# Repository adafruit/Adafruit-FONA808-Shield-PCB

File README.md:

## Adafruit FONA808 Shield PCB

<a href="http://www.adafruit.com/products/2636"><br/>
Click here to purchase one from the Adafruit shop</a>

PCB files for the Adafruit FONA808 Shield. Format is EagleCAD schematic and board layout
* https://www.adafruit.com/products/2636

### DESCRIPTION
Cellular + GPS tracking, all in one, for your Arduino? Oh yes! Introducing Adafruit FONA 808 GSM + GPS Shield, an all-in-one cellular phone module with that lets you add location-tracking, voice, text, SMS and data to your project, in Arduino shield format for easy use.

If you want a version without GPS, check out the FONA 800 Shield [here](https://www.adafruit.com/product/2468).

If you don't need the shield format, we also have this is a petite breakout [here](https://www.adafruit.com/product/2542).

If you just want a plain FONA, [click here](https://www.adafruit.com/product/1946).

This shield fits right over your Arduino or compatible. At the heart is a powerful GSM cellular module (we use the latest SIM808) with integrated GPS. This module can do just about everything

- Quad-band 850/900/1800/1900MHz - connect onto any global GSM network with any 2G SIM (in the USA, T-Mobile is suggested)
- Fully-integrated GPS (MT3337 chipset with -165 dBm tracking sensitivity) that can be controlled and query over the same serial port
- Make and receive voice calls using a headset or an external 32Ω speaker + electret microphone
- Send and receive SMS messages
- Send and receive GPRS data (TCP/IP, HTTP, etc.)
- PWM/Buzzer vibrational motor control
- AT command interface with "auto baud" detection

### License

Adafruit invests time and resources providing this open source design, please support Adafruit and open-source hardware by purchasing products from [Adafruit.com](https://www.adafruit.com)!

Designed by Adafruit Industries. 

Creative Commons Attribution, Share-Alike license, check license.txt for more information All text above must be included in any redistribution - see license.txt for more information.

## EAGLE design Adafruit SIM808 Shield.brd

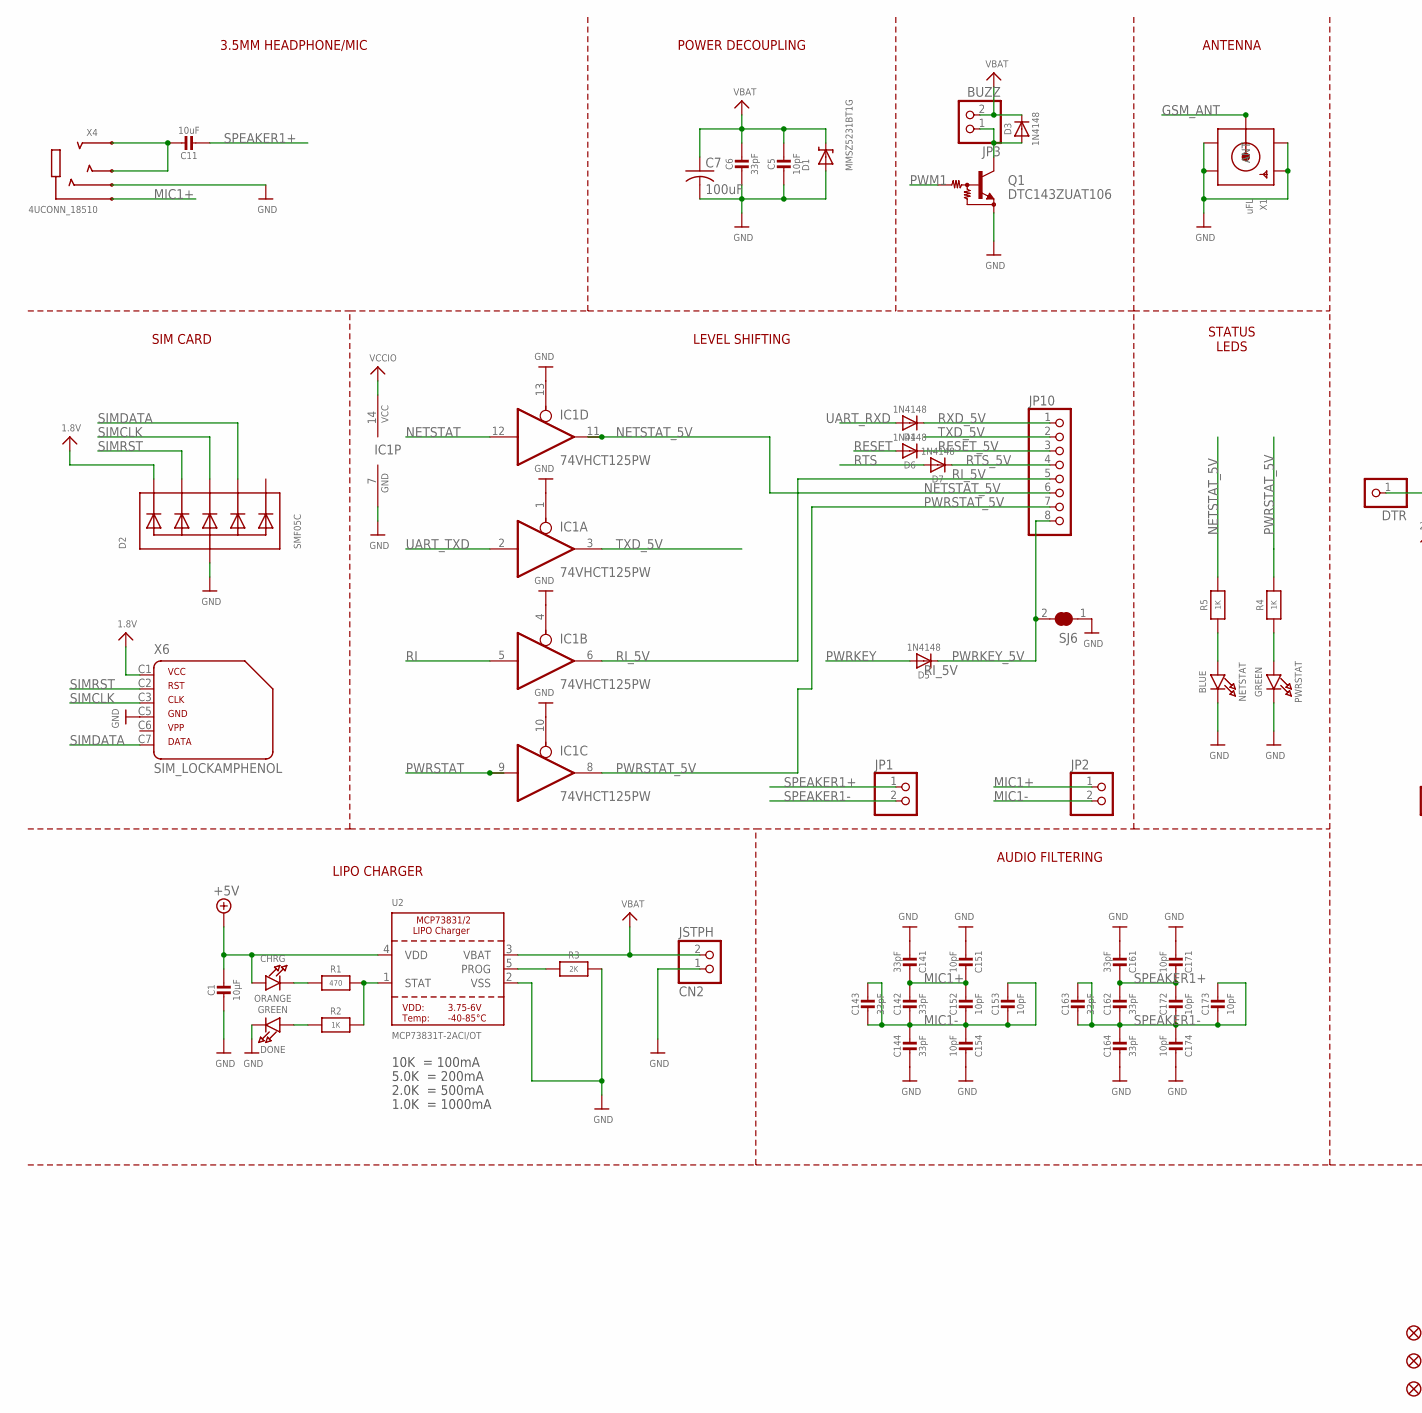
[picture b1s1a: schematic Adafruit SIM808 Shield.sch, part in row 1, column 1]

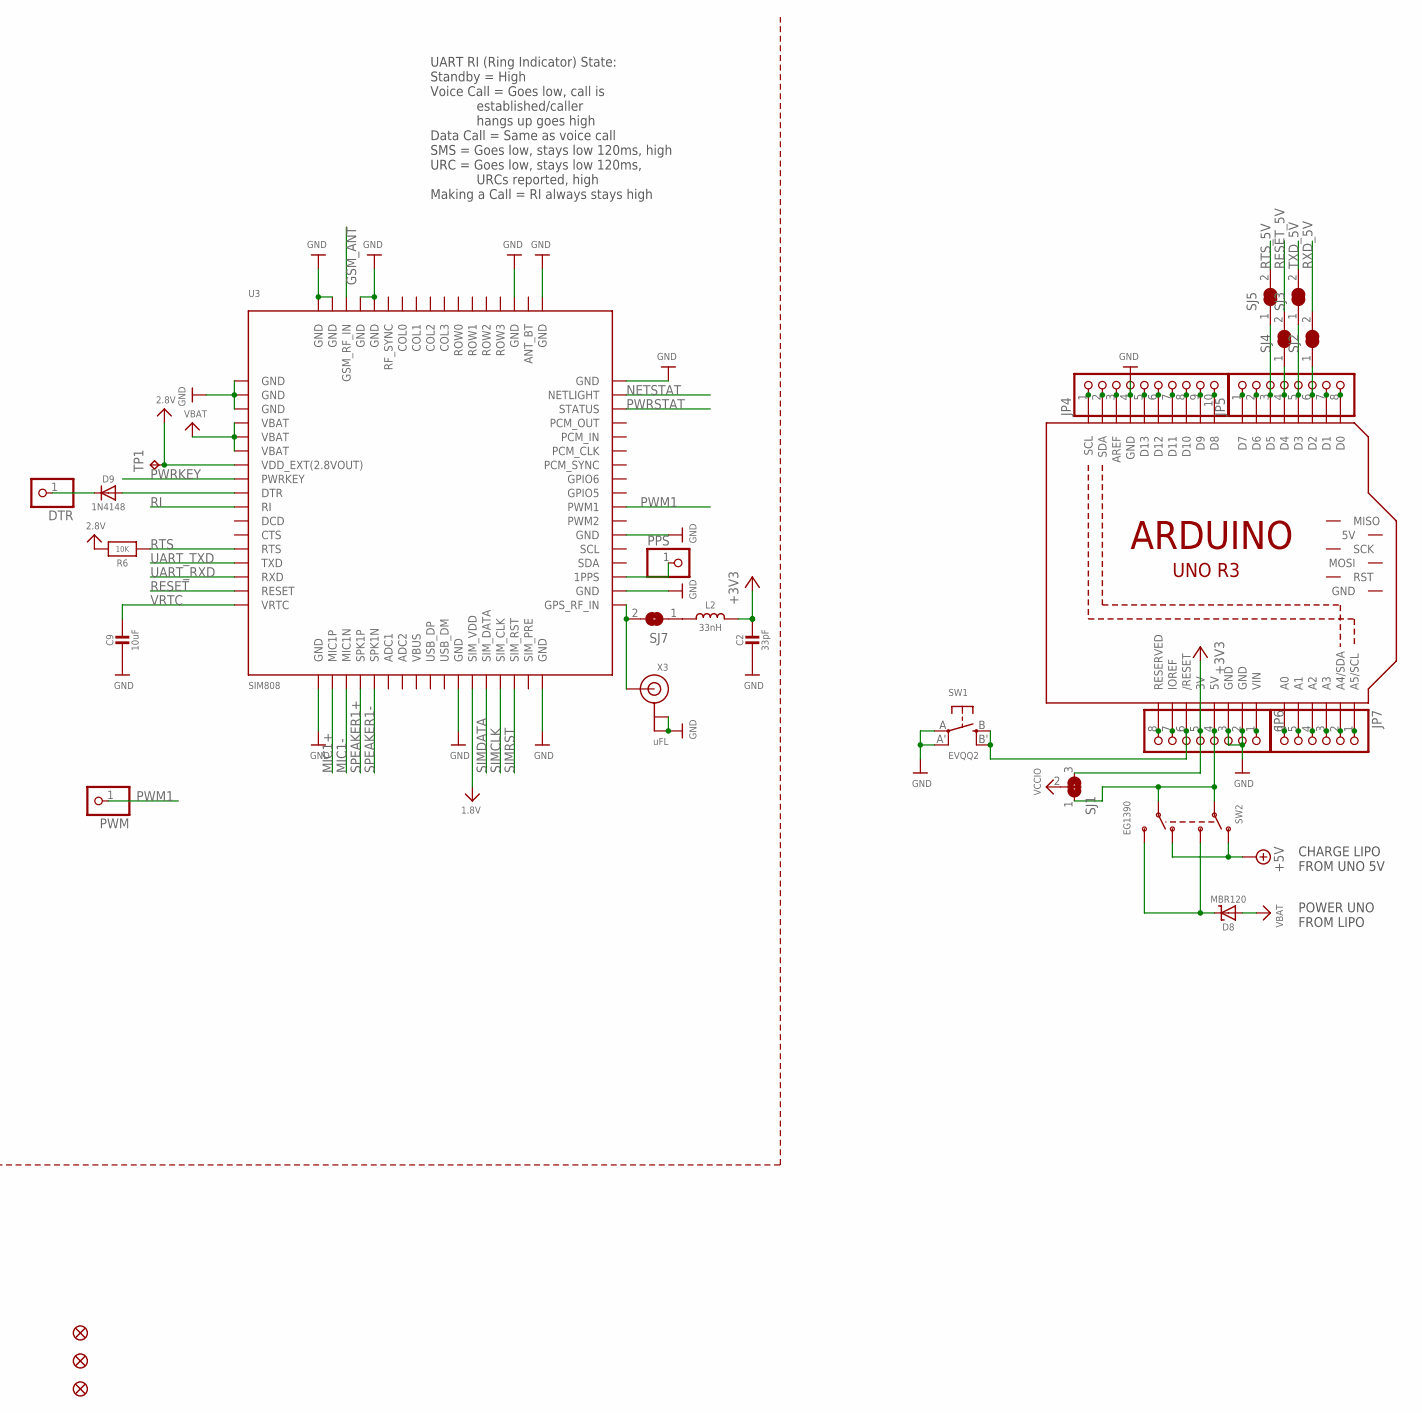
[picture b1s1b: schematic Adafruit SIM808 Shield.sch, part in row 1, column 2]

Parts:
C1: 10µF; 0805-NO
C2, C6: 33pF; 0805-NO
C5: 10pF; 0805-NO
C7: 100uF; C1210
C9, C11: 10uF; 0805-NO
C14, C16: 33pF; RESPACK_4X0603
C15, C17: 10pF; RESPACK_4X0603
CHRG: ORANGE; CHIPLED_0805_NOOUTLINE
CN2: JSTPH; JSTPH2
D1: MMSZ5231BT1G; SOD-123
D2: SMF05C; SOT363
D3, D4, D5, D6, D7, D9: 1N4148; SOD-323
D8: MBR120; SOD-123
DONE: GREEN; CHIPLED_0805_NOOUTLINE
DTR: PINHD-1X1CB; 1X01-CLEANBIG
FID1, FID2, FID3: FIDUCIAL""; FIDUCIAL_1MM
IC1: 74VHCT125PW; TSSOP14
JP1, JP2: HEADER-1X2ROUND; 1X02_ROUND
JP3: BUZZ; 1X02_ROUND
JP4: HEADER-1X1070MIL; 1X10_ROUND70
JP5, JP6: HEADER-1X876MIL; 1X08_ROUND_76
JP7: HEADER-1X676MIL; 1X06_ROUND_76
JP10: HEADER-1X870MIL; 1X08_ROUND_70
L2: 33nH; _0805MP
M1: ARDUINO_R3_ICSP_NODIM; ARDUINOR3_ICSP_NODIM
NETSTAT: BLUE; CHIPLED_0805_NOOUTLINE
PPS: PINHD-1X1CB; 1X01-CLEANBIG
PWM: PINHD-1X1CB; 1X01-CLEANBIG
PWRSTAT: GREEN; CHIPLED_0805_NOOUTLINE
Q1: DTC143ZUAT106; SC59-BEC
R1: 470; 0805-NO
R2, R4, R5: 1K; 0805-NO
R3: 2K; 0805-NO
R6: 10K; 0805-NO
SJ1: SOLDERJUMPER_2WAY; SOLDERJUMPER_2WAY_OPEN_NOPASTE
SJ2, SJ3, SJ4, SJ5, SJ6: SOLDERJUMPER_CLOSED; SOLDERJUMPER_CLOSEDWIRE
SJ7: SOLDERJUMPER; SOLDERJUMPER_ARROW_NOPASTE
SW1: EVQQ2; EVQ-Q2
SW2: EG1390
TP1: TPTP11R; TP11R
U2: MCP73831T-2ACI/OT; SOT23-5
U3: SIM808; SIM900_SMT
X1: uFL; SMA_EDGELAUNCH_UFL
X3: uFL; U.FL
X4: 4UCONN_18510
X6: SIM_LOCKAMPHENOL; C707_10M006_512_2

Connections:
1.8V: D2.1 (C1), U3.P$29 (SIM_VDD), X6.C1 (1)
2.8V: R6.2, TP1.TP, U3.P$7 (VDD_EXT(2.8VOUT))
5V: JP6.4, M1.5V, SJ1.1, SW2.P1, SW2.P2
+3V3: C2.1, JP6.5, L2.2, M1.3V, SJ1.3
+5V: C1.1, CHRG.A, SW2.O1, SW2.O2, U2.4 (VDD)
A0: JP7.6, M1.A0
A1: JP7.5, M1.A1
A2: JP7.4, M1.A2
A3: JP7.3, M1.A3
A4: JP7.2, M1.A4 (A4/SDA)
A5: JP7.1, M1.A5 (A5/SCL)
AREF: JP4.3, M1.AREF
BUZZ-: D3.A, JP3.1, Q1.C
D0: JP5.8, M1.D0
D1: JP5.7, M1.D1
D2: JP5.6, M1.D2, SJ2.1
D3: JP5.5, M1.D3, SJ3.1
D4: JP5.4, M1.D4, SJ4.1
D5: JP5.3, M1.D5, SJ5.1
D6: JP5.2, M1.D6
D7: JP5.1, M1.D7
D8: JP4.10, M1.D8
D9: JP4.9, M1.D9
D10: JP4.8, M1.D10
D11: JP4.7, M1.D11
D12: JP4.6, M1.D12
D13: JP4.5, M1.D13
DTR_5V: D9.C, DTR.1
GND: C1.2, C2.2, C5.2, C6.2, C7.2, C9.2, C14.5 (2), C14.8 (2), C15.4 (1), C15.8 (2), C16.5 (2), C16.8 (2), C17.4 (1), C17.8 (2), CN2.1, D1.A, D2.2 (A), DONE.C, IC1.1 (OE), IC1.4 (OE), IC1.7 (GND), IC1.10 (OE), IC1.13 (OE), JP4.4, JP6.2, JP6.3, M1.GND, M1.GND@1 (GND), M1.GND@3 (GND), NETSTAT.C, PWRSTAT.C, Q1.E, R3.2, SJ6.1, SW1.A, SW1.A' (P1), U2.2 (VSS), U3.P$1 (GND), U3.P$2 (GND), U3.P$3 (GND), U3.P$18 (GND), U3.P$28 (GND), U3.P$34 (GND), U3.P$36 (GND), U3.P$40 (GND), U3.P$51 (GND), U3.P$52 (GND), U3.P$54 (GND), U3.P$64 (GND), U3.P$65 (GND), U3.P$67 (GND), U3.P$68 (GND), X1.GND@1 (GND1), X1.GND@2 (GND2), X1.GND@3 (GND3), X1.GND@4 (GND4), X3.1 (GND), X3.2 (GND), X4.4-INNER_SLEEVE (RING1), X6.C5 (4)
GPS_PPS: PPS.1, U3.P$37 (1PPS)
GSM_ANT: U3.P$66 (GSM_RF_IN), X1.P (ANT)
HP+: C11.1, X4.2-TIP (RING3), X4.3-OUTER_SLEEVE (RING2)
IOREF: JP6.7, M1.IOREF
MIC1+: C14.1, C14.2 (1), C15.1, C15.2 (1), JP2.1, U3.P$19 (MIC1P), X4.1-GND (TIP)
MIC1-: C14.3 (1), C14.4 (1), C14.6 (2), C14.7 (2), C15.3 (1), C15.5 (2), C15.6 (2), C15.7 (2), JP2.2, U3.P$20 (MIC1N)
unnamed: CHRG.C, R1.1
unnamed: R1.2, R2.2, U2.1 (STAT)
unnamed: SJ7.2, U3.P$35 (GPS_RF_IN), X3.3 (SIGNAL)
unnamed: PWRSTAT.A, R4.1
unnamed: R3.1, U2.5 (PROG)
unnamed: DONE.A, R2.1
unnamed: NETSTAT.A, R5.1
unnamed: D8.C, SW2.S1, SW2.S2
unnamed: L2.1, SJ7.1
unnamed: D9.A, U3.P$9 (DTR)
NC: JP6.8, M1.RESERVED
NETSTAT: IC1.12 (I), U3.P$50 (NETLIGHT)
NETSTAT_5V: IC1.11 (O), JP10.6, R5.2
PWM1: PWM.1, Q1.B, U3.P$42 (PWM1)
PWRKEY: D5.A, U3.P$8 (PWRKEY)
PWRKEY_5V: D5.C, JP10.8, SJ6.2
PWRSTAT: IC1.9 (I), U3.P$49 (STATUS)
PWRSTAT_5V: IC1.8 (O), JP10.7, R4.2
RESET: D6.A, U3.P$16 (RESET)
RESET_5V: D6.C, JP10.3, SJ4.2
RI: IC1.5 (I), U3.P$10 (RI)
RI_5V: IC1.6 (O), JP10.5
RST: JP6.6, M1.RESET (/RESET), SW1.B (S), SW1.B' (S1)
RTS: D7.A, R6.1, U3.P$13 (RTS)
RTS_5V: D7.C, JP10.4, SJ5.2
RXD_5V: D4.C, JP10.1, SJ2.2
SCL: JP4.1, M1.SCL
SDA: JP4.2, M1.SDA
SIMCLK: D2.4 (C3), U3.P$31 (SIM_CLK), X6.C3 (3)
SIMDATA: D2.5 (C4), U3.P$30 (SIM_DATA), X6.C7 (6)
SIMRST: D2.3 (C2), U3.P$32 (SIM_RST), X6.C2 (2)
SPEAKER1+: C11.2, C16.1, C16.2 (1), C17.1, C17.2 (1), JP1.1, U3.P$21 (SPK1P)
SPEAKER1-: C16.3 (1), C16.4 (1), C16.6 (2), C16.7 (2), C17.3 (1), C17.5 (2), C17.6 (2), C17.7 (2), JP1.2, U3.P$22 (SPK1N)
TXD_5V: IC1.3 (O), JP10.2, SJ3.2
UART_RXD: D4.A, U3.P$15 (RXD)
UART_TXD: IC1.2 (I), U3.P$14 (TXD)
VBAT: C5.1, C6.1, C7.1, CN2.2, D1.C, D3.C, D8.A, JP3.2, U2.3 (VBAT), U3.P$4 (VBAT), U3.P$5 (VBAT), U3.P$6 (VBAT)
VBUS: U3.P$25 (VBUS)
VCCIO: IC1.14 (VCC), SJ1.2
VIN: JP6.1, M1.VIN
VRTC: C9.1, U3.P$17 (VRTC)

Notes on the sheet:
10K = 100mA
5.0K = 200mA
2.0K = 500mA
1.0K = 1000mA
UART RI (Ring Indicator) State: Standby = High Voice Call = Goes low, call is established/caller hangs up goes high Data Call = Same as voice call SMS = Goes low, stays low 120ms, high URC = Goes low, stays low 120ms, URCs reported, high Making a Call = RI always stays high
ANTENNA
POWER DECOUPLING
3.5MM HEADPHONE/MIC
SIM CARD
LEVEL SHIFTING
LIPO CHARGER
AUDIO FILTERING
STATUS LEDS
CHARGE LIPO FROM UNO 5V
POWER UNO FROM LIPO

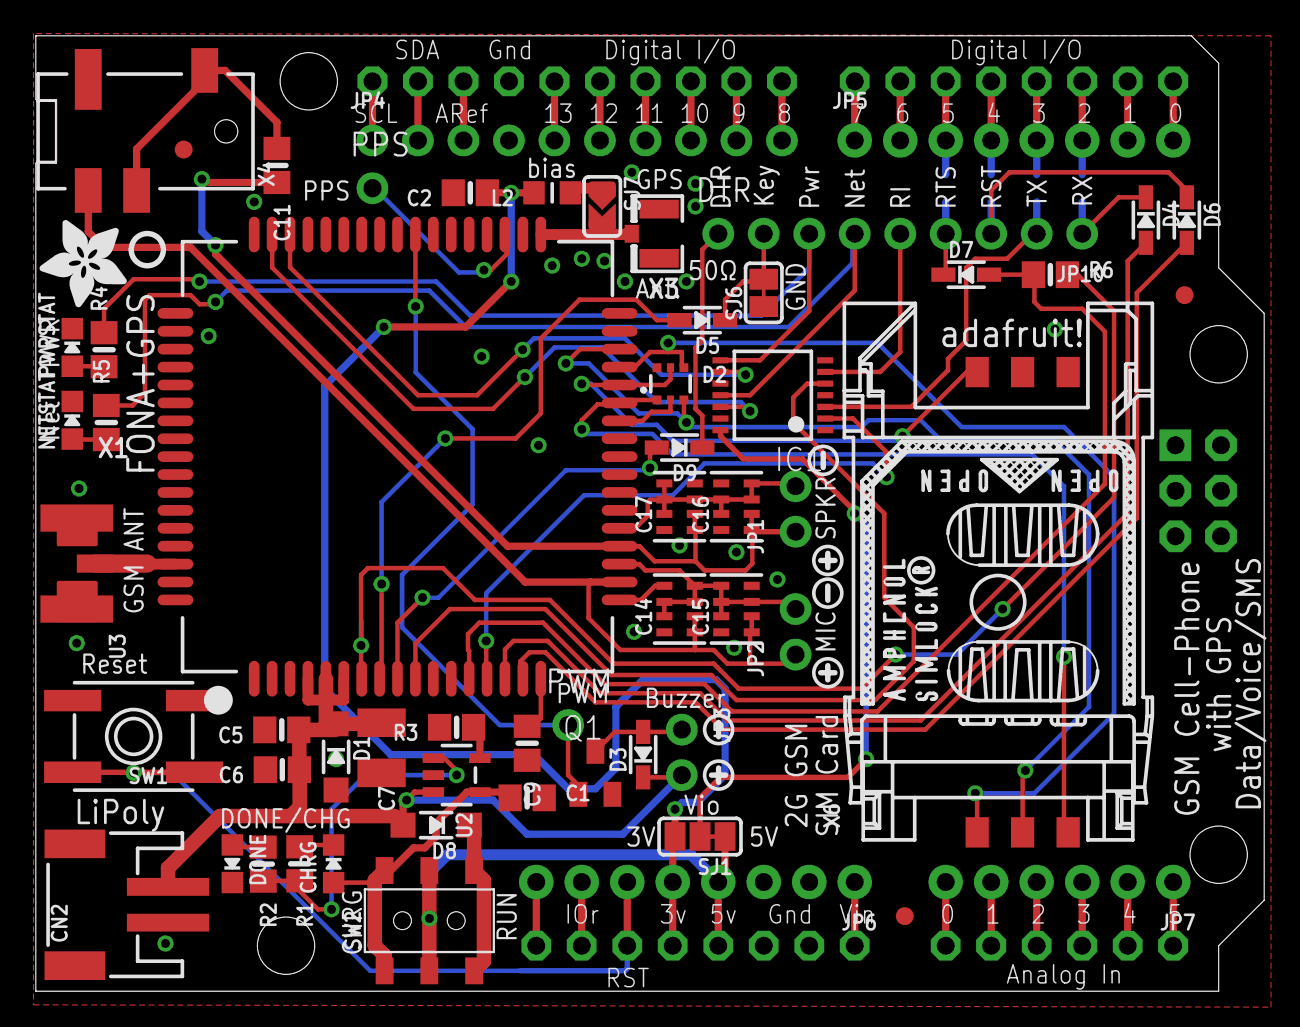
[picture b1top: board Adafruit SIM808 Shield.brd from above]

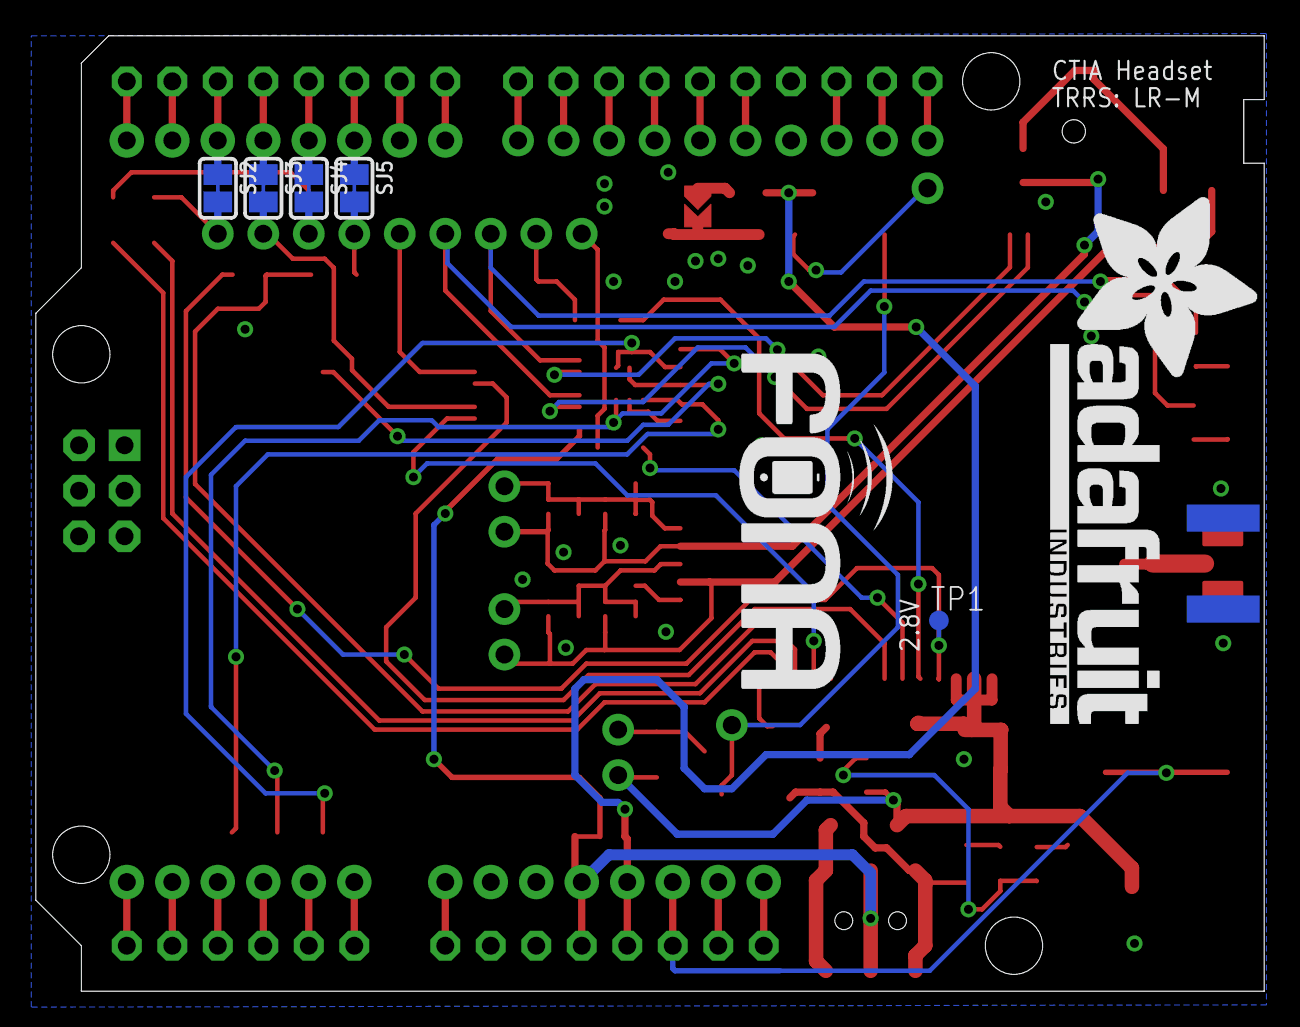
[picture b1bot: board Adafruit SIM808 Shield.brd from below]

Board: 2 copper layers, 68.6 x 53.3 mm, 75 parts (7 on the bottom side), 75 nets.

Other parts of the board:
U$2, U$20, U$35: SYMBOL_PLUS
U$25: ADAFRUIT_TEXT_30MM
U$26: FONA_LOGO
U$33, U$34, U$41: SYMBOL_MINUS
U$36: ADAFRUIT_5MM
U$64: PCBFEAT-REV-040

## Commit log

2016-09-28 init

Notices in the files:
parts and their libraries:
microbuilder: This work is placed in the public domain, and may be freely used for commercial and non-commercial work with the following conditions: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
